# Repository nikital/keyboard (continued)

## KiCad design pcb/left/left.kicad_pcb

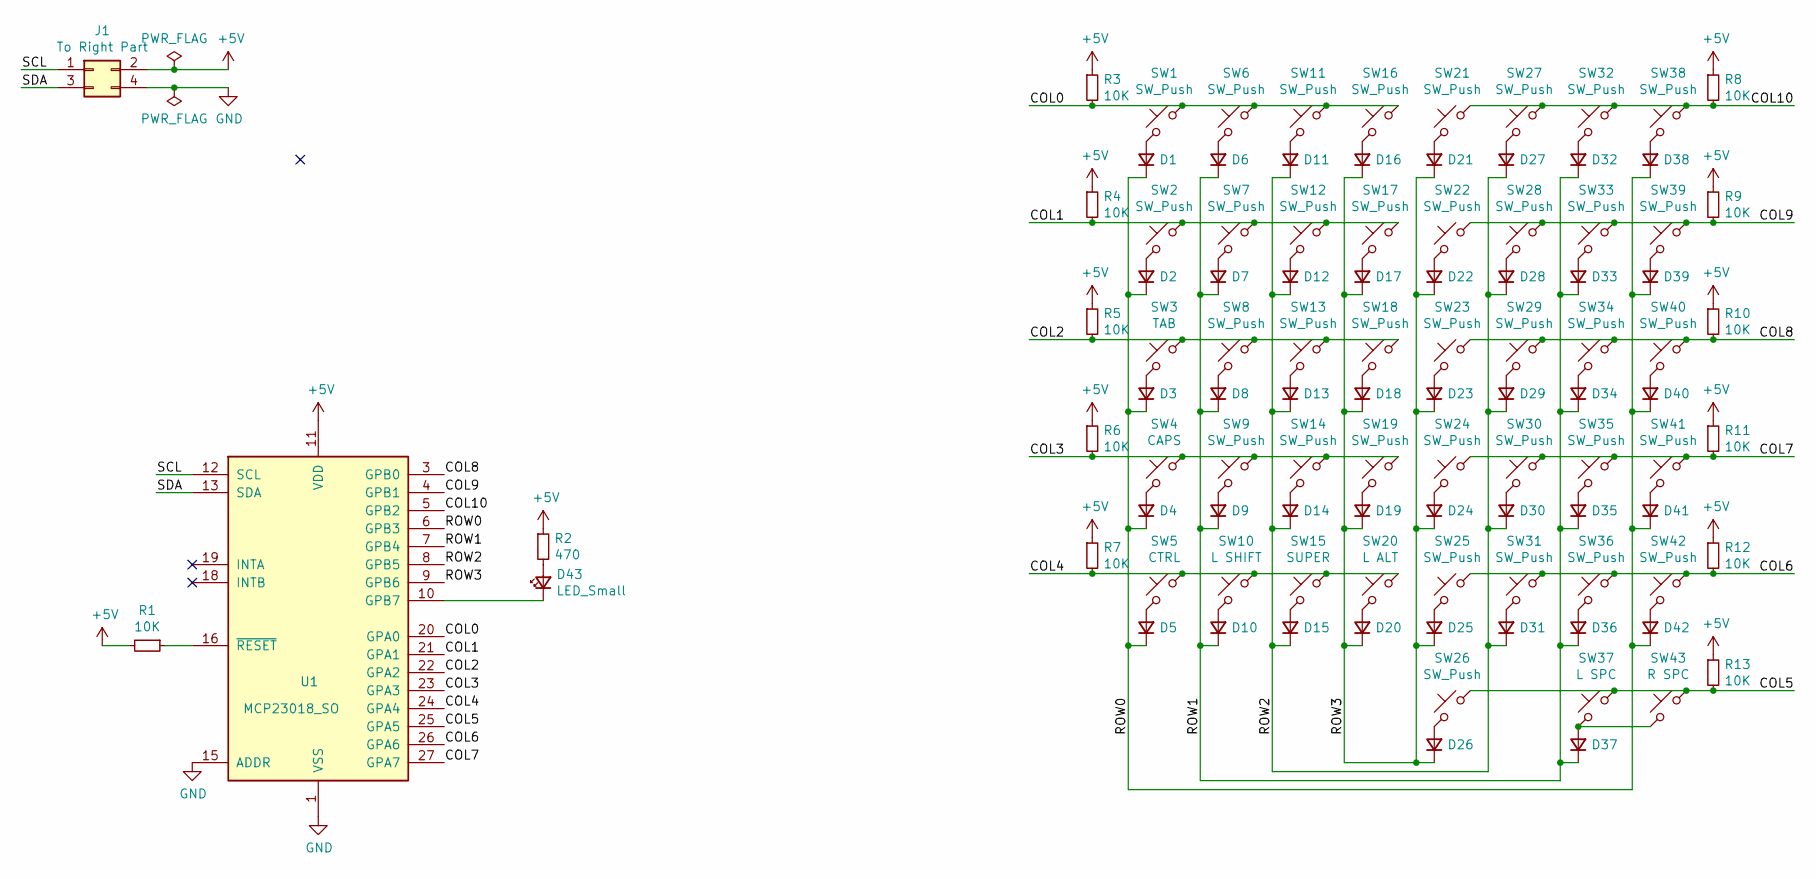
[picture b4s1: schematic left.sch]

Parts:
D1, D2, D3, D4, D5, D6, D7, D8, D9, D10, D11, D12, D13, D14, D15, D16, D17, D18, D19, D20, D21, D22, D23, D24, D25, D26, D27, D28, D29, D30, D31, D32, D33, D34, D35, D36, D37, D38, D39, D40, D41, D42: D_Small; D_SOD-123
D43: LED_Small; LED_0805_2012Metric_Pad1.15x1.40mm_HandSolder
J1: To Right Part; PinHeader_2x02_P2.54mm_Vertical
R1, R3, R4, R5, R6, R7, R8, R9, R10, R11, R12, R13: 10K; R_0805_2012Metric_Pad1.20x1.40mm_HandSolder
R2: 470; R_0805_2012Metric_Pad1.20x1.40mm_HandSolder
SW1, SW2, SW6, SW7, SW8, SW9, SW11, SW12, SW13, SW14, SW16, SW17, SW18, SW19, SW21, SW22, SW23, SW24, SW25, SW26, SW27, SW28, SW29, SW30, SW31, SW32, SW33, SW34, SW35, SW36, SW38, SW39, SW40, SW41, SW42: SW_Push; SW_Cherry_MX_1.00u_PCB
SW3: TAB; SW_Cherry_MX_1.50u_PCB
SW4: CAPS; SW_Cherry_MX_1.75u_PCB
SW5: CTRL; SW_Cherry_MX_1.25u_PCB
SW10: L SHIFT; SW_Cherry_MX_2.25u_PCB
SW15: SUPER; SW_Cherry_MX_1.25u_PCB
SW20: L ALT; SW_Cherry_MX_1.25u_PCB
SW37: L SPC; SW_Cherry_MX_2.75u_PCB
SW43: R SPC; SW_Cherry_MX_2.25u_PCB
U1: MCP23018_SO; SOIC-28W_7.5x17.9mm_P1.27mm

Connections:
+5V: J1.2, R1.2, R2.1, R3.1, R4.1, R5.1, R6.1, R7.1, R8.1, R9.1, R10.1, R11.1, R12.1, R13.1, U1.11 (VDD)
/COL0: R3.2, SW1.1, SW6.1, SW11.1, SW16.1, U1.20 (GPA0)
/COL1: R4.2, SW2.1, SW7.1, SW12.1, SW17.1, U1.21 (GPA1)
/COL2: R5.2, SW3.1, SW8.1, SW13.1, SW18.1, U1.22 (GPA2)
/COL3: R6.2, SW4.1, SW9.1, SW14.1, SW19.1, U1.23 (GPA3)
/COL4: R7.2, SW5.1, SW10.1, SW15.1, SW20.1, U1.24 (GPA4)
/COL5: R13.2, SW26.1, SW37.1, SW43.1, U1.25 (GPA5)
/COL6: R12.2, SW25.1, SW31.1, SW36.1, SW42.1, U1.26 (GPA6)
/COL7: R11.2, SW24.1, SW30.1, SW35.1, SW41.1, U1.27 (GPA7)
/COL8: R10.2, SW23.1, SW29.1, SW34.1, SW40.1, U1.3 (GPB0)
/COL9: R9.2, SW22.1, SW28.1, SW33.1, SW39.1, U1.4 (GPB1)
/COL10: R8.2, SW21.1, SW27.1, SW32.1, SW38.1, U1.5 (GPB2)
/ROW0: D1.1 (K), D2.1 (K), D3.1 (K), D4.1 (K), D5.1 (K), D38.1 (K), D39.1 (K), D40.1 (K), D41.1 (K), D42.1 (K), U1.6 (GPB3)
/ROW1: D6.1 (K), D7.1 (K), D8.1 (K), D9.1 (K), D10.1 (K), D32.1 (K), D33.1 (K), D34.1 (K), D35.1 (K), D36.1 (K), D37.1 (K), U1.7 (GPB4)
/ROW2: D11.1 (K), D12.1 (K), D13.1 (K), D14.1 (K), D15.1 (K), D27.1 (K), D28.1 (K), D29.1 (K), D30.1 (K), D31.1 (K), U1.8 (GPB5)
/ROW3: D16.1 (K), D17.1 (K), D18.1 (K), D19.1 (K), D20.1 (K), D21.1 (K), D22.1 (K), D23.1 (K), D24.1 (K), D25.1 (K), D26.1 (K), U1.9 (GPB6)
/SCL: J1.1, U1.12 (SCL)
/SDA: J1.3, U1.13 (SDA)
GND: J1.4, U1.1 (VSS), U1.15 (ADDR)
unnamed: D1.2 (A), SW1.2
unnamed: D2.2 (A), SW2.2
unnamed: D3.2 (A), SW3.2
unnamed: D4.2 (A), SW4.2
unnamed: D5.2 (A), SW5.2
unnamed: D6.2 (A), SW6.2
unnamed: D7.2 (A), SW7.2
unnamed: D8.2 (A), SW8.2
unnamed: D9.2 (A), SW9.2
unnamed: D10.2 (A), SW10.2
unnamed: D11.2 (A), SW11.2
unnamed: D12.2 (A), SW12.2
unnamed: D13.2 (A), SW13.2
unnamed: D14.2 (A), SW14.2
unnamed: D15.2 (A), SW15.2
unnamed: D16.2 (A), SW16.2
unnamed: D17.2 (A), SW17.2
unnamed: D18.2 (A), SW18.2
unnamed: D19.2 (A), SW19.2
unnamed: D20.2 (A), SW20.2
unnamed: D21.2 (A), SW21.2
unnamed: D22.2 (A), SW22.2
unnamed: D23.2 (A), SW23.2
unnamed: D24.2 (A), SW24.2
unnamed: D25.2 (A), SW25.2
unnamed: D26.2 (A), SW26.2
unnamed: D27.2 (A), SW27.2
unnamed: D28.2 (A), SW28.2
unnamed: D29.2 (A), SW29.2
unnamed: D30.2 (A), SW30.2
unnamed: D31.2 (A), SW31.2
unnamed: D32.2 (A), SW32.2
unnamed: D33.2 (A), SW33.2
unnamed: D34.2 (A), SW34.2
unnamed: D35.2 (A), SW35.2
unnamed: D36.2 (A), SW36.2
unnamed: D37.2 (A), SW37.2, SW43.2
unnamed: D38.2 (A), SW38.2
unnamed: D39.2 (A), SW39.2
unnamed: D40.2 (A), SW40.2
unnamed: D41.2 (A), SW41.2
unnamed: D42.2 (A), SW42.2
unnamed: D43.1 (K), U1.10 (GPB7)
unnamed: D43.2 (A), R2.2
unnamed: R1.1, U1.16 (~RESET)

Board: 2 copper layers, 101 parts (43 on the bottom side), 64 nets, no tracks yet.

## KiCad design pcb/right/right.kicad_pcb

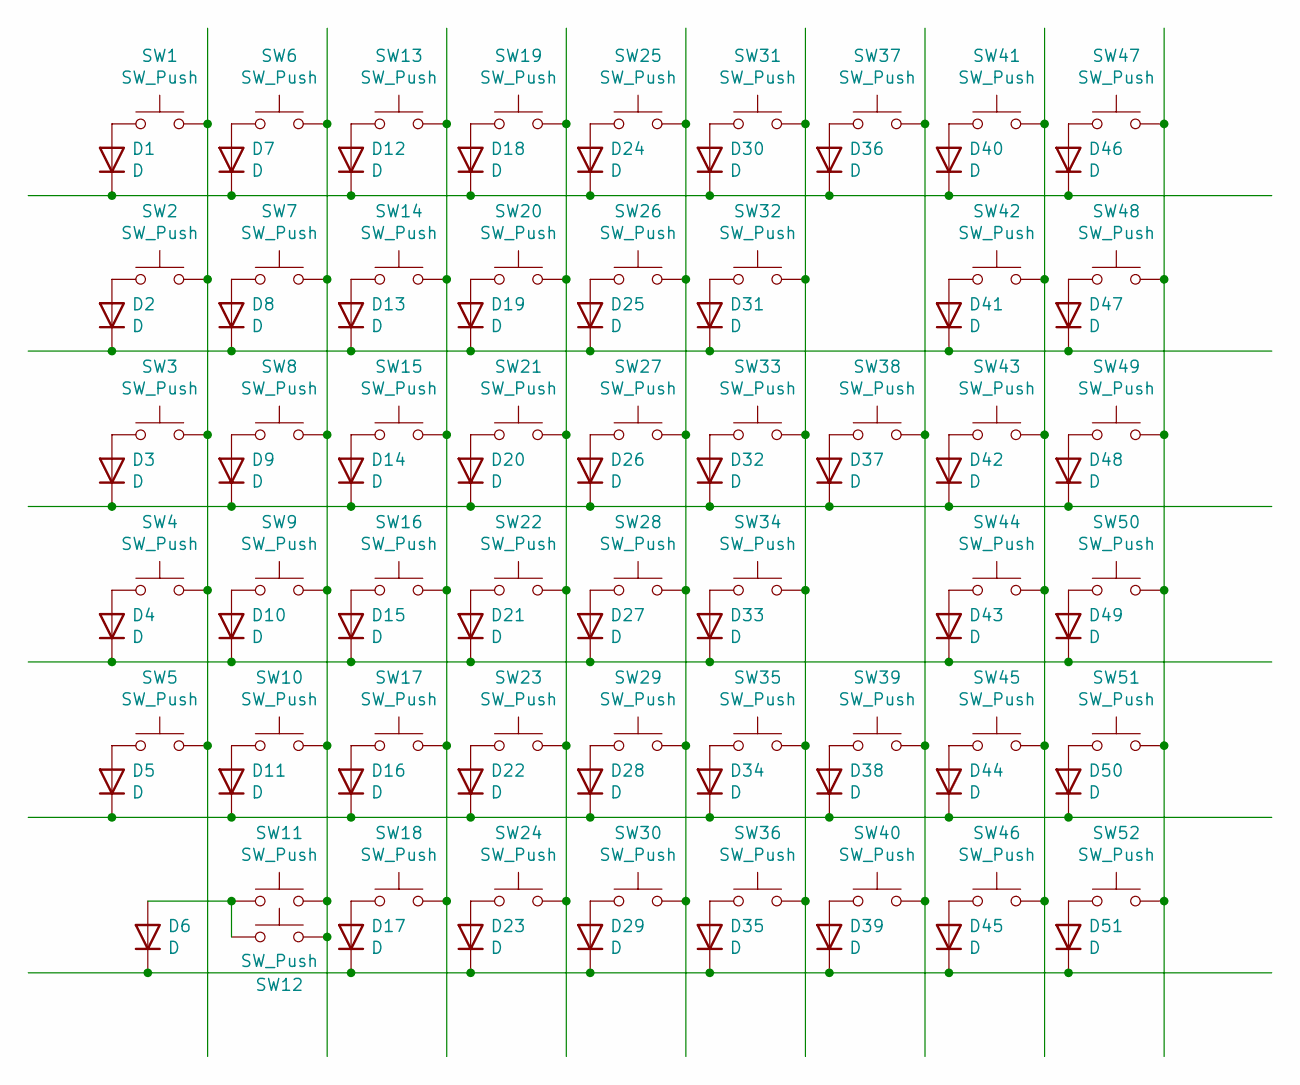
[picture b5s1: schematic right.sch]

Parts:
D1, D2, D3, D4, D5, D6, D7, D8, D9, D10, D11, D12, D13, D14, D15, D16, D17, D18, D19, D20, D21, D22, D23, D24, D25, D26, D27, D28, D29, D30, D31, D32, D33, D34, D35, D36, D37, D38, D39, D40, D41, D42, D43, D44, D45, D46, D47, D48, D49, D50, D51: D; D_SOD-123
SW1, SW2, SW3, SW4, SW5, SW6, SW7, SW8, SW9, SW10, SW13, SW14, SW15, SW16, SW17, SW18, SW19, SW20, SW21, SW22, SW23, SW24, SW25, SW26, SW27, SW28, SW29, SW30, SW31, SW32, SW33, SW34, SW35, SW36, SW37, SW38, SW40, SW41, SW45, SW46, SW47, SW48, SW49, SW50, SW51, SW52: SW_Push; SW_Cherry_MX_1.00u_PCB
SW11, SW44: SW_Push; SW_Cherry_MX_2.25u_PCB
SW12: SW_Push; SW_Cherry_MX_2.75u_PCB
SW39: SW_Push; SW_Cherry_MX_1.75u_PCB
SW42: SW_Push; SW_Cherry_MX_2.00u_PCB
SW43: SW_Push; SW_Cherry_MX_1.50u_PCB

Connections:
unnamed: D1.1 (K), D7.1 (K), D12.1 (K), D18.1 (K), D24.1 (K), D30.1 (K), D36.1 (K), D40.1 (K), D46.1 (K)
unnamed: D1.2 (A), SW1.1
unnamed: D2.2 (A), SW2.1
unnamed: D3.2 (A), SW3.1
unnamed: D4.2 (A), SW4.1
unnamed: D5.2 (A), SW5.1
unnamed: D6.2 (A), SW11.1, SW12.1
unnamed: D7.2 (A), SW6.1
unnamed: D8.2 (A), SW7.1
unnamed: D9.2 (A), SW8.1
unnamed: D4.1 (K), D10.1 (K), D15.1 (K), D21.1 (K), D27.1 (K), D33.1 (K), D43.1 (K), D49.1 (K)
unnamed: D10.2 (A), SW9.1
unnamed: D5.1 (K), D11.1 (K), D16.1 (K), D22.1 (K), D28.1 (K), D34.1 (K), D38.1 (K), D44.1 (K), D50.1 (K)
unnamed: D11.2 (A), SW10.1
unnamed: D12.2 (A), SW13.1
unnamed: D2.1 (K), D8.1 (K), D13.1 (K), D19.1 (K), D25.1 (K), D31.1 (K), D41.1 (K), D47.1 (K)
unnamed: D13.2 (A), SW14.1
unnamed: D3.1 (K), D9.1 (K), D14.1 (K), D20.1 (K), D26.1 (K), D32.1 (K), D37.1 (K), D42.1 (K), D48.1 (K)
unnamed: D14.2 (A), SW15.1
unnamed: D15.2 (A), SW16.1
unnamed: D16.2 (A), SW17.1
unnamed: D6.1 (K), D17.1 (K), D23.1 (K), D29.1 (K), D35.1 (K), D39.1 (K), D45.1 (K), D51.1 (K)
unnamed: D17.2 (A), SW18.1
unnamed: D18.2 (A), SW19.1
unnamed: D19.2 (A), SW20.1
unnamed: D20.2 (A), SW21.1
unnamed: D21.2 (A), SW22.1
unnamed: D22.2 (A), SW23.1
unnamed: D23.2 (A), SW24.1
unnamed: D24.2 (A), SW25.1
unnamed: D25.2 (A), SW26.1
unnamed: D26.2 (A), SW27.1
unnamed: D27.2 (A), SW28.1
unnamed: D28.2 (A), SW29.1
unnamed: D29.2 (A), SW30.1
unnamed: D30.2 (A), SW31.1
unnamed: D31.2 (A), SW32.1
unnamed: D32.2 (A), SW33.1
unnamed: D33.2 (A), SW34.1
unnamed: D34.2 (A), SW35.1
unnamed: D35.2 (A), SW36.1
unnamed: D36.2 (A), SW37.1
unnamed: D37.2 (A), SW38.1
unnamed: D38.2 (A), SW39.1
unnamed: D39.2 (A), SW40.1
unnamed: D40.2 (A), SW41.1
unnamed: D41.2 (A), SW42.1
unnamed: D42.2 (A), SW43.1
unnamed: D43.2 (A), SW44.1
unnamed: D44.2 (A), SW45.1
unnamed: D45.2 (A), SW46.1
unnamed: D46.2 (A), SW47.1
unnamed: D47.2 (A), SW48.1
unnamed: D48.2 (A), SW49.1
unnamed: D49.2 (A), SW50.1
unnamed: D50.2 (A), SW51.1
unnamed: D51.2 (A), SW52.1
unnamed: SW1.2, SW2.2, SW3.2, SW4.2, SW5.2
unnamed: SW6.2, SW7.2, SW8.2, SW9.2, SW10.2, SW11.2, SW12.2
unnamed: SW13.2, SW14.2, SW15.2, SW16.2, SW17.2, SW18.2
unnamed: SW19.2, SW20.2, SW21.2, SW22.2, SW23.2, SW24.2
unnamed: SW25.2, SW26.2, SW27.2, SW28.2, SW29.2, SW30.2
unnamed: SW31.2, SW32.2, SW33.2, SW34.2, SW35.2, SW36.2
unnamed: SW37.2, SW38.2, SW39.2, SW40.2
unnamed: SW41.2, SW42.2, SW43.2, SW44.2, SW45.2, SW46.2
unnamed: SW47.2, SW48.2, SW49.2, SW50.2, SW51.2, SW52.2

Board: 2 copper layers, 103 parts (51 on the bottom side), 66 nets, no tracks yet.

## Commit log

2020-10-13 Layouts
2020-10-13 layout: Add another key left of space
2020-10-13 layout: Move to separate folder
2020-10-17 plate: Generate
2020-10-17 readme: Add
2020-10-17 docs: ATMEGA23U4
2020-10-24 layout: Logical matrix
2020-10-24 readme: Document components
2020-10-25 pcb: Right schematic
2020-10-25 right: Assign footprint + netlist
2020-10-25 pcb: Right key layout
2020-11-07 pcb: Ignore stuff
2020-11-07 pcb: right: Shrink spacebar stab hole
2020-11-07 pcb: right: Update Design Rules to JLCPCB
2020-11-07 pcb: right: diodes
2021-02-22 docs: EMI
2021-02-22 pcb: right: Revert small spacebar hole
2021-02-24 docs: Add more docs
2021-02-24 pcb: right: Power to MCU
2021-02-25 pcb: Right: Reset
2021-02-26 pcb: right: ICSP, I2C
2021-02-27 pcb: right: Finish schematics
2021-02-27 pcb: right: annotate
2021-02-27 pcb: right: PWR_FLAG for EDC
2021-02-27 pcb: right: Footprint for ICSP and left part connector
2021-03-01 pcb: right: pullup for keys and i2c
2021-03-01 layout: New matrix with only 4 scanlines
2021-03-01 pcb: left: matrix schematic
2021-03-01 pcb: MCP23018 symbol
2021-03-02 pcb: left: schema
2021-03-02 pcb: left: annotate
2021-03-02 pcb: left: assign footprints
2021-03-02 pcb: left: netlist
2021-03-02 pcb: left: Layout keys
2021-03-03 pcb: left: JLCPCB design rules
2021-03-05 pcb: right: fuse size
2021-03-05 doc: case info
2021-03-06 pcb: right: Tanatalum capacitor
2021-03-06 pcb: Micro USB footprint
2021-03-06 pcb: RJ12 footprint
2021-03-06 pcb: poc: schematic
2021-03-06 pcb: poc: Assign footprints
2021-03-09 pcb: poc: JLCPCB design rules
2021-03-30 pcb: poc: Some routing
2021-03-31 pcb: poc: Routed nabaz stuff
2021-04-01 pcb: poc: Routed buttons and breakout
2021-04-01 pcb: poc: Change 2x11 to 2x10 breakout
2021-04-01 pcb: poc: i2c breakout and crystal ground
2021-04-01 pcb: poc: MCP side layout
2021-04-01 pcb: poc: Finished?
2021-04-01 pcb: poc: silkscreen
2021-04-03 pcb: poc: Make USB track 0.25
2021-04-03 pcb: poc: Change track to 0.4mm
2021-04-03 pcb: poc: Space out left side
2021-06-17 pcb: poc: routed left side except breakout
2021-06-17 pcb: poc: Route left breakout
2021-06-17 pcb: poc: Make left breakout smaller
2021-06-27 pcb: poc: Silkscreen adjustment
2021-06-27 pcb: poc: Move stiching via for clock
2021-06-27 pcb: poc: Sign the PCB
2021-06-27 pcb: poc: Export gerbers
2021-08-21 pcb: poc: annotate capacitor
2021-08-21 dfu: Download bootloaders
2021-08-21 fw: helloavr: Toy firmware
2021-08-21 fw: Import qmk submodule
2021-08-21 fw: Implement POC
2021-09-04 layout: Slash layout and matrix
2021-09-05 pcb: Fix USB pinout
2021-09-05 pcb: slash_left: new project
2021-09-05 pcb: slash_left: add symbols and footprints
2021-09-06 pcb: slash_left: Schematic
2021-09-06 layout: slash: Rework right matrix
2021-09-06 pcb: slash_right: Start schematic
2021-09-08 layout: slash: Split space
2021-09-08 fw: Try using SPI pins for input
2021-09-08 pcb: Add Kailh sockets footprints
2021-09-10 pcb: slash_right: General electronics
2021-10-01 pcb: slash: Matrix schematic
2021-10-08 pcb: slash_righ: Fill missing values
2021-10-08 pcb: slash_right: Annotate
2021-10-08 pcb: slash_right: Assign footprints
2021-10-09 pcb: slash_right: Layout switches
2021-10-09 pcb: slash_righ: Place switches
2021-10-09 pcb: slash_right: rough layout
2021-10-09 pcb: slash_right: Add PWR symbol
2021-10-10 layout: Update slash
2021-10-10 plate: slash from swillkb
2021-10-23 plate: slash: right
2021-10-23 pcb: slash: right: Start routing
2021-10-24 pcb: slash: right: Continue
2021-11-13 pcb: slash: Progress
2021-11-15 pcb: slash: more routing
2021-11-28 pcb: slash: right: Finish routing
2021-11-28 pcb: slash: right: Tune USB diff pair
2021-12-01 plate: slash: left
2021-12-02 pcb: slash: left: Assign footprints
2021-12-12 pcb: slash: left: Routing
2021-12-15 pcb: slash: left: finish
2021-12-19 plate: slash: Rename file
2021-12-19 pcb: slash: Silkscreen adjustment for production
2021-12-19 pcb: slash: left: Add PWR flags
2021-12-19 pcb: slash: Plot gerbers
2021-12-23 plate: slash: Holes
2021-12-29 plate: slash: straighten edge
2022-01-08 fw: clangd config
2022-01-19 fw: Update qmk
2022-01-19 plate: slash: Add holes for reset button and crystal
2022-06-02 plate: slash: Add production files
2022-07-01 fw: Keymap updates
2024-10-04 fw: New QMK
2024-10-04 readme: Document command
2024-10-07 fw: Backup
